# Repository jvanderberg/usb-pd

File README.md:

# usb-pd

A pocket USB-C PD/PPS bench supply, 67 x 17 mm. Plug it into a PD charger and pick a fixed voltage. With a PPS
charger, set any voltage from 5 to 21 V in 100 mV steps, plus a current limit. Switch the output on and off and read
volts, amps and board temperature on a tiny OLED.

*KiCad 3D renders. The 0.69" OLED is hand-soldered by its flex cable and folded over onto the board. Its model
(`tools/oled_3d.py`) is built from the panel's outline drawing and shows a real frame from the firmware.*

## The screen

What the firmware draws, rendered on the host from the real UI and OLED code through a model of the panel's memory
(`cd firmware && make screens`):

| | |
|---|---|
| PPS, output on: voltage, temperature, current, current limit |  |
| PPS, editing the voltage (`>` marks the value being edited) |  |
| PPS, editing the current limit (UP + DOWN switches) |  |
| PPS, undervoltage trip (e.g. the charger hit its current limit) |  |
| Fixed voltage, output on |  |
| Fixed voltage, output off |  |
| No PD charger (plain 5 V) |  |
| Thermal cutoff |  |
| Over-current trip |  |

## What it does

- **PD sink:** AP33772S (AP33772SDKZ-13-FA02). It negotiates the charger's fixed voltages and PPS up to 21 V, and
  never requests what the charger does not offer. EPR is disabled in firmware.
- **Buttons:** four, in one row: `[ON]  [SEL]  [UP][DN]`.
  - ON switches the output on and off.
  - SEL steps through the fixed voltages the charger offers, then PPS, turning the output off first.
  - In PPS, UP / DOWN change the setpoint (hold to accelerate), and UP + DOWN together switch between voltage and
    current limit.
- **Display:** voltage, current and NTC temperature, all read from the AP33772S.
- **Memory:** remembers the last voltage or PPS setpoint and the on/off state, wear-levelled in the MCU's DataFlash.
- **Protection:** the AP33772S's OCP / OVP / UVP / OTP, plus the firmware's own thermal trip (board NTC and a
  MOSFET temperature estimate).
- **Firmware updates** over the same USB-C port (CH552 ROM bootloader).

## Hardware

- 67 x 17 mm, 2 layers, all parts on top, made for JLCPCB economic assembly.
- **ICs:** CH552P MCU and AP33772S PD sink, with SGM2203 (5 V) and XC6206 (3.3 V) regulators.
- **Output switch:** one AON7262E N-MOSFET driven by the AP33772S, with an SS34 clamp and 10 uF on the output, as on
  CentyLab's RotoPD.
- **I2C:** the MCU talks to the AP33772S on its own 5 V bus and to the OLED on a 3.3 V bus.
- **Output:** two 5.08 mm through-hole pads, for a screw terminal or wires.
- **Design method:** designed in KiCad 10 from scripts with [kicad-skills](https://github.com/jvanderberg/kicad-skills).
  The schematic, netlist, placement and routing are generated by `tools/` (`tools/build_board.sh`).

Read these before building one:
- [docs/requirements.md](docs/requirements.md): requirements, decisions, block diagram and parts.
- [docs/design-review.md](docs/design-review.md): the design review, including its main limit. The board is
  small, so 100 W continuous makes it too hot; the thermal trips are what protect it.

Production files for JLCPCB (gerbers, BOM, CPL, part check) for 10 boards are in `production/`. To regenerate them:
`jlcimport-cli production hardware/usbpd.kicad_pcb -n 10 -o production`.

## Firmware

C for SDCC, in [firmware/](firmware/). See [firmware/README.md](firmware/README.md).

```
cd firmware
make          # build/usbpd.hex and .bin
make test     # host tests
make screens  # the screen images above
make flash    # wchisp, with the board in its bootloader (hold SEL while plugging in)
```

## Status

Designed, not yet built. The board passes DRC, ERC and the design review, and the firmware passes its host tests,
but nothing has run on real hardware. Known open items before or at bring-up:
- **Firmware:** confirm that "output off" took effect by reading `SYSTEM` back, at boot and on every trip.
- **Bring-up:** measure Q1's gate drive and on-resistance, and check that JLC placed the polarised parts correctly.
- **Behaviour:** when a PPS charger hits its current limit, the output trips on undervoltage instead of holding a
  constant current.

This is a hobby project, not designed or reviewed for safety-critical use.

Created in [T3 Code](https://t3.codes).

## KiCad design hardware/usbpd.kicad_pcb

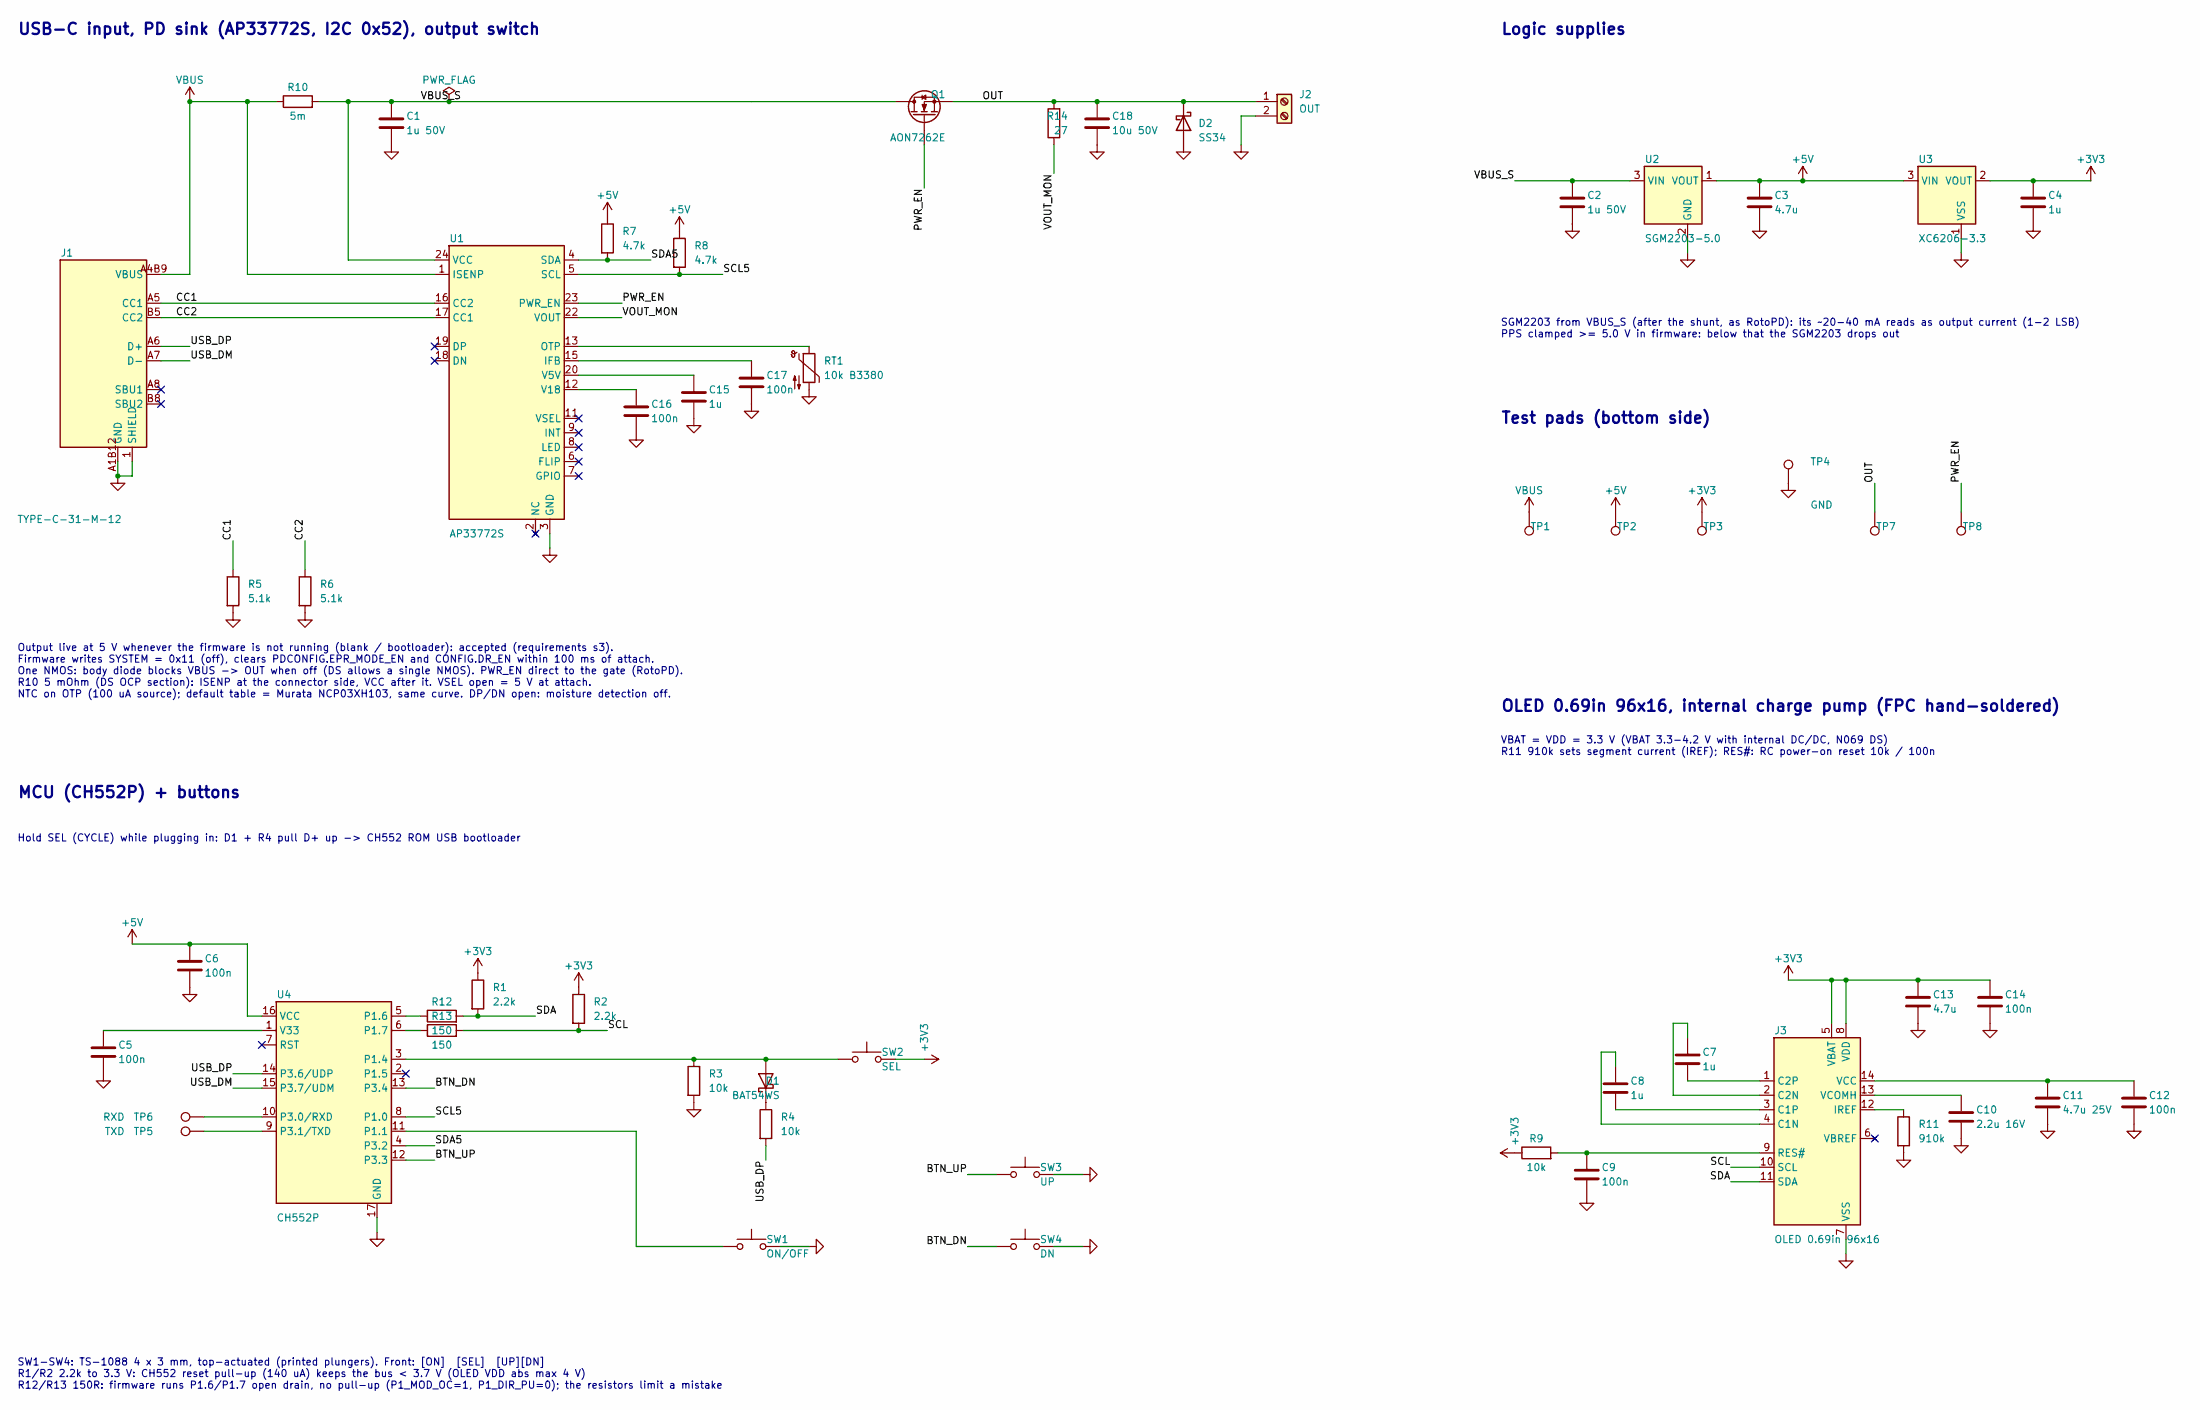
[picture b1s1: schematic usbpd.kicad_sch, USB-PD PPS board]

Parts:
C1, C2: 1u 50V; CL21B105KBFNNNE; LCSC C28323
C3, C13: 4.7u; CL05A475MP5NRNC; LCSC C23733
C4, C7, C8, C15: 1u; CL05A105KA5NQNC; LCSC C52923
C5, C6, C9, C12, C14, C16, C17: 100n; CL05B104KO5NNNC; LCSC C1525
C10: 2.2u 16V; CL10A225KO8NNNC; LCSC C23630
C11: 4.7u 25V; CL10A475KA8NQNC; LCSC C69335
C18: 10u 50V; CL31A106KBHNNNE; LCSC C13585
D1: BAT54WS; BAT54WS_C7502694; LCSC C7502694
D2: SS34; SS34_C8678; LCSC C8678
J1: TYPE-C-31-M-12; Manufacturer Part TYPE-C-31-M-12; LCSC C165948
J2: OUT; TerminalBlock_Phoenix_MKDS-1,5-2-5.08_1x02_P5.08mm_Horizont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
J3: OLED 0.69in 96x16; OLED_0.69in_96x16_FPC14
Q1: AON7262E; Manufacturer Part AON7262E; LCSC C176755
R1, R2: 2.2k; 0402WGF2201TCE; LCSC C25879
R3, R4, R9: 10k; 0402WGF1002TCE; LCSC C25744
R5, R6: 5.1k; 0402WGF5101TCE; LCSC C25905
R7, R8: 4.7k; 0402WGF4701TCE; LCSC C25900
R10: 5m; RLM12FTCMR005; LCSC C316225
R11: 910k; 0402WGF9103TCE; LCSC C25800
R12, R13: 150; 0402WGF1500TCE; LCSC C25082
R14: 27; 0402WGF270JTCE; LCSC C25100
RT1: 10k B3380; NCP15XH103F03RC; LCSC C77131
SW1: ON/OFF; TS-1088-AR02016; LCSC C720477
SW2: SEL; TS-1088-AR02016; LCSC C720477
SW3: UP; TS-1088-AR02016; LCSC C720477
SW4: DN; TS-1088-AR02016; LCSC C720477
TP1: VBUS; TestPoint_Pad_D1.0mm
TP2: +5V; TestPoint_Pad_D1.0mm
TP3: +3V3; TestPoint_Pad_D1.0mm
TP4: GND; TestPoint_Pad_D1.0mm
TP5: TXD; TestPoint_Pad_D1.0mm
TP6: RXD; TestPoint_Pad_D1.0mm
TP7: OUT; TestPoint_Pad_D1.0mm
TP8: PWR_EN; TestPoint_Pad_D1.0mm
U1: AP33772S; AP33772S_EPVIA; Manufacturer Part AP33772SDKZ-13-FA02; LCSC C50341643
U2: SGM2203-5.0; SGM2203-5_0YK3G_TR; Manufacturer Part SGM2203-5.0YK3G/TR; LCSC C4555390
U3: XC6206-3.3; XC6206P332MR; Manufacturer Part XC6206P332MR-G; LCSC C5446
U4: CH552P; CH552P_EPVIA; Manufacturer Part CH552P; LCSC C968536

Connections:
+3V3: C4.1, C13.1, C14.1, J3.5 (VBAT), J3.8 (VDD), R1.1, R2.1, R9.1, SW2.2, TP3.1 (1_1), U3.2 (VOUT)
+5V: C3.1, C6.1, R7.1, R8.1, TP2.1 (1_1), U2.1 (VOUT), U3.3 (VIN), U4.16 (VCC)
/BTN_DN: SW4.1, U4.13 (P3.4)
/BTN_UP: SW3.1, U4.12 (P3.3)
/CC1: J1.A5 (CC1), R5.1, U1.16 (CC2)
/CC2: J1.B5 (CC2), R6.1, U1.17 (CC1)
/OUT: C18.1, D2.1 (K), J2.1, Q1.1 (S), Q1.2 (S), Q1.3 (S), R14.2, TP7.1 (1_1)
/PWR_EN: Q1.4 (G), TP8.1 (1_1), U1.23 (PWR_EN)
/SCL: J3.10 (SCL), R2.2, R13.2
/SCL5: R8.2, U1.5 (SCL), U4.8 (P1.0)
/SDA: J3.11 (SDA), R1.2, R12.2
/SDA5: R7.2, U1.4 (SDA), U4.4 (P3.2)
/USB_DM: J1.A7 (D-), J1.B7 (D-), U4.15 (P3.7/UDM)
/USB_DP: J1.A6 (D+), J1.B6 (D+), R4.2, U4.14 (P3.6/UDP)
/VBUS_S: C1.1, C2.1, Q1.5 (D), R10.2, U1.24 (VCC), U2.3 (VIN)
/VOUT_MON: R14.1, U1.22 (VOUT)
GND: C1.2, C2.2, C3.2, C4.2, C5.2, C6.2, C9.2, C10.2, C11.2, C12.2, C13.2, C14.2, C15.2, C16.2, C17.2, C18.2, D2.2 (A), J1.1 (SHIELD), J1.2 (SHIELD), J1.3 (SHIELD), J1.4 (SHIELD), J1.A1B12 (GND), J1.B1A12 (GND), J2.2, J3.7 (VSS), R3.2, R5.2, R6.2, R11.2, RT1.2, SW1.2, SW3.2, SW4.2, TP4.1 (1_1), U1.3 (GND), U1.25 (GND), U2.2 (GND), U3.1 (VSS), U4.17 (GND)
unnamed: D1.2 (A), R3.1, SW2.1, U4.3 (P1.4)
unnamed: D1.1 (K), R4.1
unnamed: C8.1, J3.4 (C1N)
unnamed: C8.2, J3.3 (C1P)
unnamed: C7.1, J3.2 (C2N)
unnamed: C7.2, J3.1 (C2P)
unnamed: J3.12 (IREF), R11.1
unnamed: C9.1, J3.9 (RES#), R9.2
unnamed: C11.1, C12.1, J3.14 (VCC)
unnamed: C10.1, J3.13 (VCOMH)
unnamed: C17.1, U1.15 (IFB)
unnamed: RT1.1, U1.13 (OTP)
unnamed: C15.1, U1.20 (V5V)
unnamed: C16.1, U1.12 (V18)
unnamed: SW1.1, U4.11 (P1.1)
unnamed: R12.1, U4.5 (P1.6)
unnamed: R13.1, U4.6 (P1.7)
unnamed: TP6.1 (1_1), U4.10 (P3.0/RXD)
unnamed: TP5.1 (1_1), U4.9 (P3.1/TXD)
unnamed: C5.1, U4.1 (V33)
VBUS: J1.A4B9 (VBUS), J1.B4A9 (VBUS), R10.1, TP1.1 (1_1), U1.1 (ISENP)

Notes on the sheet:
USB-C input, PD sink (AP33772S, I2C 0x52), output switch
Output live at 5 V whenever the firmware is not running (blank / bootloader): accepted (requirements s3). Firmware writes SYSTEM = 0x11 (off), clears PDCONFIG.EPR_MODE_EN and CONFIG.DR_EN within 100 ms of attach. One NMOS: body diode blocks VBUS -> OUT when off (DS allows a single NMOS). PWR_EN dir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
Logic supplies
SGM2203 from VBUS_S (after the shunt, as RotoPD): its ~20-40 mA reads as output current (1-2 LSB) PPS clamped >= 5.0 V in firmware: below that the SGM2203 drops out
MCU (CH552P) + buttons
Hold SEL (CYCLE) while plugging in: D1 + R4 pull D+ up -> CH552 ROM USB bootloader
SW1-SW4: TS-1088 4 x 3 mm, top-actuated (printed plungers). Front: [ON] [SEL] [UP][DN] R1/R2 2.2k to 3.3 V: CH552 reset pull-up (140 uA) keeps the bus < 3.7 V (OLED VDD abs max 4 V) R12/R13 150R: firmware runs P1.6/P1.7 open drain, no pull-up (P1_MOD_OC=1, P1_DIR_PU=0); the resistors limit a mistake
OLED 0.69in 96x16, internal charge pump (FPC hand-soldered)
VBAT = VDD = 3.3 V (VBAT 3.3-4.2 V with internal DC/DC, N069 DS) R11 910k sets segment current (IREF); RES#: RC power-on reset 10k / 100n
Test pads (bottom side)

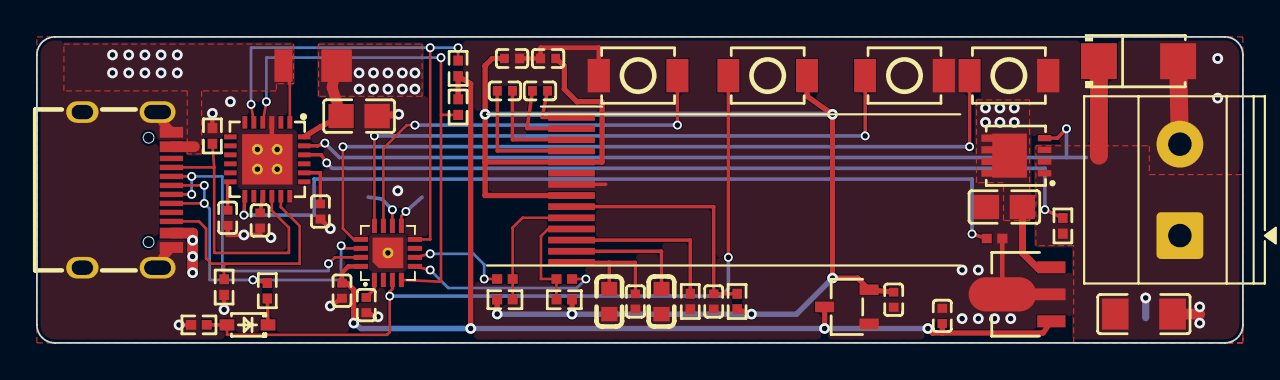
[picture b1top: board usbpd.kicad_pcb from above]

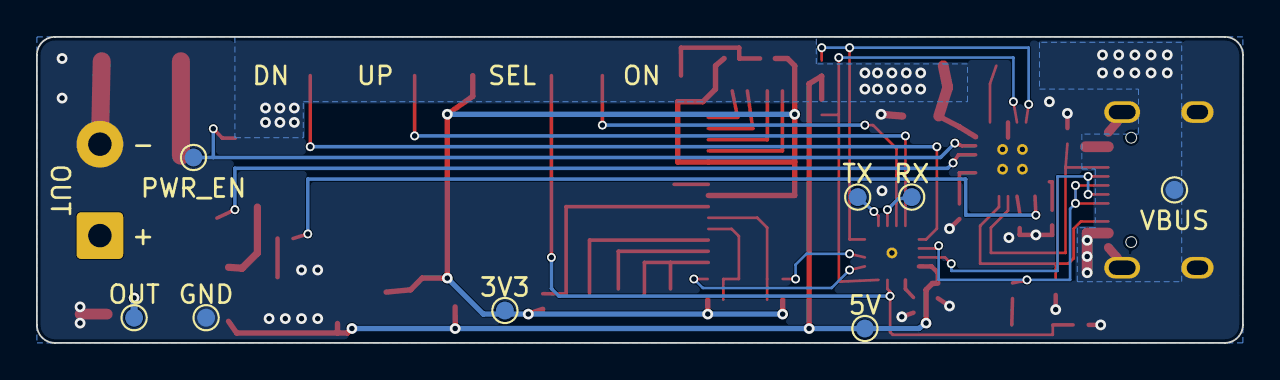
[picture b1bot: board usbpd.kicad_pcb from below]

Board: 2 copper layers, 67.0 x 17.0 mm, 55 parts (8 on the bottom side), 38 nets.

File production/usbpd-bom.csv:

Comment,Designator,Footprint,JLCPCB Part #
1u 50V,"C1,C2",CL21B105KBFNNNE,C28323
4.7u,"C3,C13",CL05A475MP5NRNC,C23733
1u,"C4,C7,C8,C15",CL05A105KA5NQNC,C52923
100n,"C5,C6,C9,C12,C14,C16,C17",CL05B104KO5NNNC,C1525
2.2u 16V,C10,CL10A225KO8NNNC,C23630
4.7u 25V,C11,CL10A475KA8NQNC,C69335
10u 50V,C18,CL31A106KBHNNNE,C13585
BAT54WS,D1,BAT54WS_C7502694,C7502694
SS34,D2,SS34_C8678,C8678
TYPE-C-31-M-12,J1,TYPE-C-31-M-12,C165948
AON7262E,Q1,AON7262E,C176755
2.2k,"R1,R2",0402WGF2201TCE,C25879
10k,"R3,R4,R9",0402WGF1002TCE,C25744
5.1k,"R5,R6",0402WGF5101TCE,C25905
4.7k,"R7,R8",0402WGF4701TCE,C25900
5m,R10,RLM12FTCMR005,C316225
910k,R11,0402WGF9103TCE,C25800
150,"R12,R13",0402WGF1500TCE,C25082
27,R14,0402WGF270JTCE,C25100
10k B3380,RT1,NCP15XH103F03RC,C77131
ON/OFF / SEL / UP / DN,"SW1,SW2,SW3,SW4",TS-1088-AR02016,C720477
AP33772S,U1,AP33772S_EPVIA,C50341643
SGM2203-5.0,U2,SGM2203-5_0YK3G_TR,C4555390
XC6206-3.3,U3,XC6206P332MR,C5446
CH552P,U4,CH552P_EPVIA,C968536

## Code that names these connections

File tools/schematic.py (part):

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for pin, net in (('A5', 'CC1'), ('B5', 'CC2')):
    s.label(net, *L(j1.p(pin), 2.54))
# USB data pair leaves the block (CH552 bootloader only; AP33772S DP/DN open)
for pin, net in (('A6', 'USB_DP'), ('A7', 'USB_DM')):
    p = j1.p(pin)
    s.wire(p, L(p, 5.08)); s.label(net, *L(p, 5.08))
for pin in ('A8', 'B8'):
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s.wire(n2, (n2[0], vcc[1]), vcc)
xq = u1.p(4)[0] + 55.88                                    # Q1 sits right of U1's pull-ups and caps
s.wire(n2, L(n2, 7.62)); s.wire(L(n2, 7.62), (xq - 25.4, top))
s.label('VBUS_S', *L(n2, 12.7)); s.tap(L(n2, 12.7))
rail('PWR_FLAG', L(n2, 17.78)); s.tap(L(n2, 17.78))       # VBUS_S is fed through the shunt, not by a power pin
hang(C('C1', '1u 50V'), L(n2, 7.62))                       # VCC: 1 uF required (DS pin 24)
s.tap(L(n2, 7.62))
# Q1 AON7262E: D = VBUS_S (left), S = OUT (right), G down to PWR_EN (direct, as RotoPD)
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assert q1.p(1)[0] > q1.p(5)[0] and q1.p(4)[1] > top, 'Q1 orientation: D left, S right, G down'
s.wire((xq - 25.4, top), q1.p(5))
gq = q1.p(4)
s.wire(gq, L(gq, 0, 7.62)); s.label('PWR_EN', *L(gq, 0, 7.62), rot=270)
j2 = s.add('Connector:Screw_Terminal_01x02', 'J2', 'OUT', 0, 0,
           footprint='TerminalBlock_Phoenix:TerminalBlock_Phoenix_MKDS-1,5-2-5.08_1x02_P5.08mm_Horizontal',
           fields={'Datasheet': 'https://www.phoenixcontact.com/en-us/products/pcb-terminal-block-mkds-15-2-508-1715721'},
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# VOUT monitor: 27R from OUT to the VOUT pin (as RotoPD R12)
r14 = R('R14', '27', rot=180)
at(r14, 2, L(q1.p(1), 17.78)); s.tap(L(q1.p(1), 17.78))
s.wire(r14.p(1), L(r14.p(1), 0, 5.08)); s.label('VOUT_MON', *L(r14.p(1), 0, 5.08), rot=270)
p2 = j2.p(2); s.wire(p2, L(p2, -2.54), L(p2, -2.54, 5.08)); gnd(L(p2, -2.54, 5.08))
# output: 10 uF bulk and a Schottky clamp (as RotoPD C6 / D3): an inductive load switched off by Q1 (or by an OCP trip)
# drags OUT below ground; D2 holds it near -0.4 V, sparing Q1 and the VOUT pin (abs min -0.3 V). Reverse-biased in use.
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s.wire(scl, L(scl, 25.4)); s.label('SCL5', *L(scl, 25.4))
for ref, p, dx in (('R7', sda, 5.08), ('R8', scl, 17.78)):
    r = R(ref, '4.7k'); at(r, 2, L(p, dx)); s.tap(L(p, dx)); rail('+5V', r.p(1))
for pin, net in ((23, 'PWR_EN'), (22, 'VOUT_MON')):
    p = u1.p(pin); s.wire(p, L(p, 7.62)); s.label(net, *L(p, 7.62))
rt1 = s.add('Device:Thermistor_NTC', 'RT1', '10k B3380', 0, 0, footprint='NoOutline:NCP15XH103F03RC', lcsc='C77131',
            fields={'Datasheet': 'https://www.lcsc.com/datasheet/C77131.pdf'})
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           lcsc='C5446')
y = u2.p(3)[1]
x0 = u2.p(3)[0] - 20.32
s.wire((x0, y), u2.p(3)); s.label('VBUS_S', x0, y, rot=180)
hang(C('C2', '1u 50V'), (x0 + 10.16, y))
s.wire(u2.p(1), u3.p(3))
# SGM2203 needs 1-10 uF EFFECTIVE output capacitance (DS p.10); 4.7 uF 10 V 0402 keeps ~1.5-2 uF at 5 V
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s.wire(v33, (c5x, v33[1]))
c5 = C('C5', '100n'); at(c5, 1, (c5x, v33[1])); gnd(c5.p(2))
s.nc(u4.p(7))
for pin, net in ((14, 'USB_DP'), (15, 'USB_DM')):
    p = u4.p(pin)
    s.wire(p, L(p, -5.08)); s.label(net, *L(p, -5.08), rot=180)
for pin, ref, net in ((10, 'TP6', 'RXD'), (9, 'TP5', 'TXD')):
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gp = u4.p(17); s.wire(gp, L(gp, 0, G)); gnd(L(gp, 0, G))
s.nc(u4.p(2))                    # P1.5: alternate bootloader-entry pin, left alone
# bus B (5 V, AP33772S): P3.2 = SDA5, P1.0 = SCL5. UP / DN: P3.3 / P3.4 to GND (internal pull-ups)
for pin, net in ((4, 'SDA5'), (8, 'SCL5'), (12, 'BTN_UP'), (13, 'BTN_DN')):
    p = u4.p(pin); s.wire(p, L(p, 5.08)); s.label(net, *L(p, 5.08))
# I2C with pull-ups hanging above
sda, scl = u4.p(5), u4.p(6)
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# buttons
on, cyc = u4.p(11), u4.p(3)                 # P1.1 ON/OFF, P1.4 SEL (CYCLE)
sw1 = s.add('Switch:SW_Push', 'SW1', 'ON/OFF', 0, 0, footprint='JLCImport:TS-1088-AR02016', lcsc='C720477')
at(sw1, 1, L(on, 55.88, 20.32))                           # ON/OFF below R4's USB_DP label
s.wire(on, L(on, 40.64), L(on, 40.64, 20.32), sw1.p(1))
p = sw1.p(2); s.wire(p, L(p, 5.08)); gnd(L(p, 5.08), 90)
sw2 = s.add('Switch:SW_Push', 'SW2', 'SEL', 0, 0, footprint='JLCImport:TS-1088-AR02016', lcsc='C720477')
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           lcsc='C7502694', fields={'_ref_at': L(cyc, 66.04, 3.81), '_val_at': L(cyc, 66.04, 6.35), '_just': 'left'})
at(d1, 2, L(cyc, 63.5)); s.tap(L(cyc, 63.5))
r4 = R('R4', '10k'); at(r4, 1, d1.p(1)); s.wire(d1.p(1), r4.p(1))
p = r4.p(2); s.wire(p, L(p, 0, G)); s.label('USB_DP', *L(p, 0, G), rot=270)
for ref, val, net, x in (('SW3', 'UP', 'BTN_UP', 198.12), ('SW4', 'DN', 'BTN_DN', 198.12)):
    y0 = 226.06 if ref == 'SW3' else 238.76
    sw = s.add('Switch:SW_Push', ref, val, 0, 0, footprint='JLCImport:TS-1088-AR02016', lcsc='C720477')
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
